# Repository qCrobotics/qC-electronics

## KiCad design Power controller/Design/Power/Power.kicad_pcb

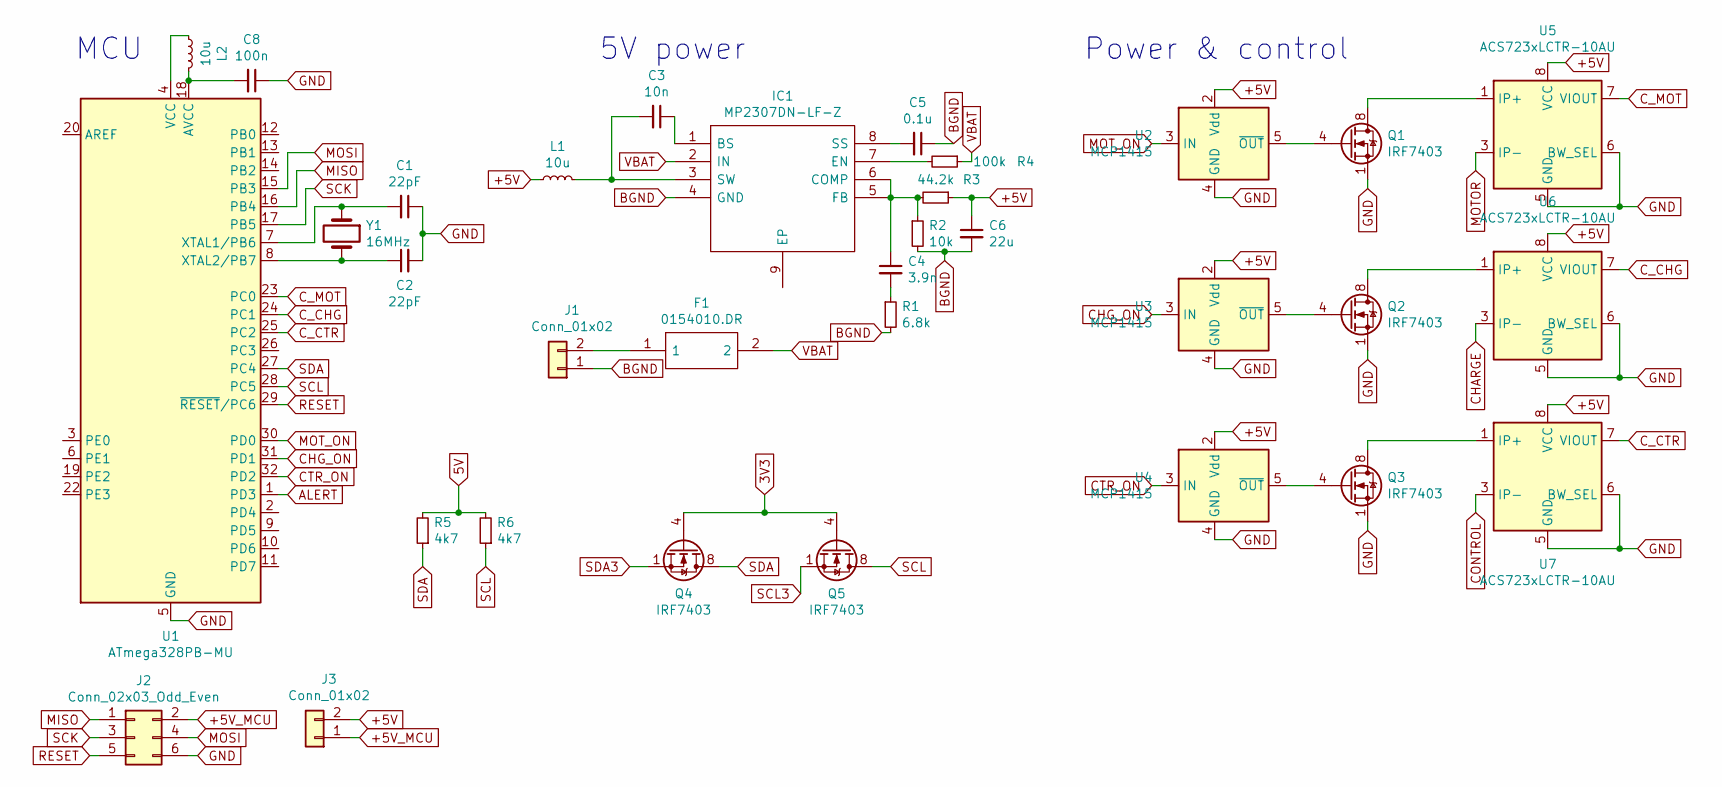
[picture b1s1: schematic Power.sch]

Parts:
C1, C2: 22pF; C_0805_2012Metric_Pad1.15x1.40mm_HandSolder
C3: 10n; C_0805_2012Metric_Pad1.15x1.40mm_HandSolder
C4: 3.9n; C_0805_2012Metric_Pad1.15x1.40mm_HandSolder
C5: 0.1u; C_0805_2012Metric_Pad1.15x1.40mm_HandSolder
C6: 22u; C_0805_2012Metric_Pad1.15x1.40mm_HandSolder
C8: 100n; C_0805_2012Metric_Pad1.15x1.40mm_HandSolder
F1: 0154010.DR; 0154001.DRT; Manufacturer_Part_Number 0154010.DR; Mouser Part Number 576-0154010.DR
IC1: MP2307DN-LF-Z; SOIC127P600X170-9N; Manufacturer_Part_Number MP2307DN-LF-Z; Mouser Part Number 946-MP2307DNLFZ
J1: Conn_01x02; Molex_Nano-Fit_105313-xx02_1x02_P2.50mm_Horizontal
J2: Conn_02x03_Odd_Even; PinHeader_2x03_P2.54mm_Vertical
J3: Conn_01x02; PinHeader_1x02_P2.54mm_Vertical
L1: 10u; L_Vishay_IHLP-2525
L2: 10u; L_1210_3225Metric_Pad1.42x2.65mm_HandSolder
Q1, Q2, Q3, Q4, Q5: IRF7403; SOIC-8_3.9x4.9mm_P1.27mm
R1: 6.8k; R_0805_2012Metric_Pad1.15x1.40mm_HandSolder
R2: 10k; R_0805_2012Metric_Pad1.15x1.40mm_HandSolder
R3: 44.2k; R_0805_2012Metric_Pad1.15x1.40mm_HandSolder
R4: 100k; R_0805_2012Metric_Pad1.15x1.40mm_HandSolder
R5, R6: 4k7; R_0805_2012Metric_Pad1.15x1.40mm_HandSolder
U1: ATmega328PB-MU; QFN-32-1EP_5x5mm_P0.5mm_EP3.1x3.1mm
U2, U3, U4: MCP1415; SOT-23-5
U5, U6, U7: ACS723xLCTR-10AU; SOIC-8_3.9x4.9mm_P1.27mm
Y1: 16MHz; Crystal_SMD_TXC_7A-2Pin_5x3.2mm

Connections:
3V3: Q4.4 (G), Q5.4 (G)
5V: R5.2, R6.2
+5V: C6.1, J3.2, L1.1, R3.1, U2.2 (Vdd), U3.2 (Vdd), U4.2 (Vdd), U5.8 (VCC), U6.8 (VCC), U7.8 (VCC)
+5V_MCU: J2.2, J3.1
ALERT: U1.1 (PD3)
BGND: C5.1, C6.2, IC1.4 (GND), J1.1, R1.2, R2.2
CHARGE: U6.3 (IP-), U6.4 (IP-)
CHG_ON: U1.31 (PD1), U3.3 (IN)
CONTROL: U7.3 (IP-), U7.4 (IP-)
CTR_ON: U1.32 (PD2), U4.3 (IN)
C_CHG: U1.24 (PC1), U6.7 (VIOUT)
C_CTR: U1.25 (PC2), U7.7 (VIOUT)
C_MOT: U1.23 (PC0), U5.7 (VIOUT)
GND: C1.1, C2.2, C8.1, J2.6, Q1.1 (S), Q1.2 (S), Q1.3 (S), Q2.1 (S), Q2.2 (S), Q2.3 (S), Q3.1 (S), Q3.2 (S), Q3.3 (S), U1.5 (GND), U1.21 (GND), U1.33 (GND), U2.4 (GND), U3.4 (GND), U4.4 (GND), U5.5 (GND), U5.6 (BW_SEL), U6.5 (GND), U6.6 (BW_SEL), U7.5 (GND), U7.6 (BW_SEL)
MISO: J2.1, U1.16 (PB4)
MOSI: J2.4, U1.15 (PB3)
MOTOR: U5.3 (IP-), U5.4 (IP-)
MOT_ON: U1.30 (PD0), U2.3 (IN)
unnamed: C1.2, U1.7 (XTAL1/PB6), Y1.1
unnamed: C2.1, U1.8 (XTAL2/PB7), Y1.2
unnamed: C3.1, IC1.1 (BS)
unnamed: C3.2, IC1.3 (SW), L1.2
unnamed: C4.1, IC1.5 (FB), IC1.6 (COMP), R2.1, R3.2
unnamed: C4.2, R1.1
unnamed: C5.2, IC1.8 (SS)
unnamed: C8.2, L2.2, U1.18 (AVCC)
unnamed: F1.1, J1.2
unnamed: IC1.7 (EN), R4.2
unnamed: L2.1, U1.4 (VCC)
unnamed: Q1.4 (G), U2.5 (~OUT)
unnamed: Q1.5 (D), Q1.6 (D), Q1.7 (D), Q1.8 (D), U5.1 (IP+), U5.2 (IP+)
unnamed: Q2.4 (G), U3.5 (~OUT)
unnamed: Q2.5 (D), Q2.6 (D), Q2.7 (D), Q2.8 (D), U6.1 (IP+), U6.2 (IP+)
unnamed: Q3.4 (G), U4.5 (~OUT)
unnamed: Q3.5 (D), Q3.6 (D), Q3.7 (D), Q3.8 (D), U7.1 (IP+), U7.2 (IP+)
RESET: J2.5, U1.29 (~RESET~/PC6)
SCK: J2.3, U1.17 (PB5)
SCL: Q5.5 (D), Q5.6 (D), Q5.7 (D), Q5.8 (D), R6.1, U1.28 (PC5)
SCL3: Q5.1 (S), Q5.2 (S), Q5.3 (S)
SDA: Q4.5 (D), Q4.6 (D), Q4.7 (D), Q4.8 (D), R5.1, U1.27 (PC4)
SDA3: Q4.1 (S), Q4.2 (S), Q4.3 (S)
VBAT: F1.2, IC1.2 (IN), R4.1

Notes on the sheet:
Power & control
MCU
5V power

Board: 2 copper layers, 33 parts (0 on the bottom side), 41 nets, no tracks yet.

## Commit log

2018-12-15 Initial commit, project created
2019-01-02 First design
2019-01-14 Added ICSP, assigned footprints
2019-03-04 Removed fuel gauge, grouped PCB
